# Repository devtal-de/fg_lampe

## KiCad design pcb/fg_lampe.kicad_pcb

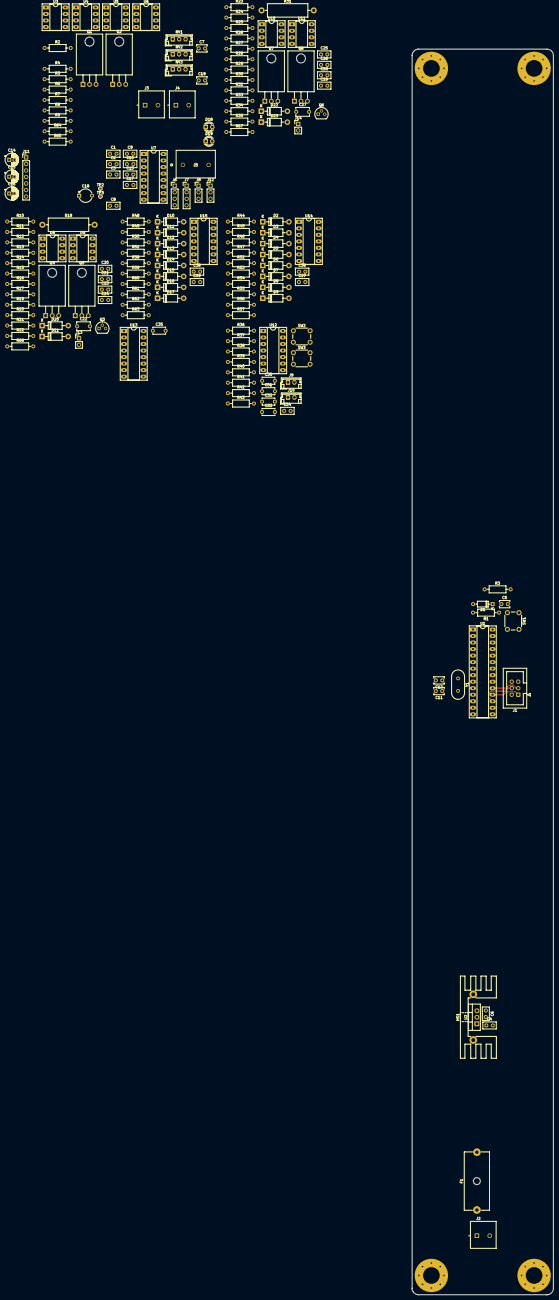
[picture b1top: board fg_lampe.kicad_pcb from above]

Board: 2 copper layers, 55.0 x 485.0 mm, 181 parts (0 on the bottom side), 110 nets.

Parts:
C1, C2, C3, C6, C8, C9, C10, C13, C17, C20, C21, C23, C24, C25, C26, C28, C29, C34, C36, C37, C38, C39: 0.1uF; C_Disc_D5.0mm_W2.5mm_P2.50mm
C4: 0.33uF; C_Disc_D5.0mm_W2.5mm_P2.50mm
C5: 10nF; C_Disc_D3.8mm_W2.6mm_P2.50mm
C7, C19: 1uF; C_Disc_D3.8mm_W2.6mm_P2.50mm
C11, C12: 22pF; C_Disc_D3.8mm_W2.6mm_P2.50mm
C14, C15, C16: 10uF; CP_Radial_D5.0mm_P2.00mm
C18: 10uF; CP_Radial_Tantal_D5.0mm_P5.00mm
C22, C27: 2.2nF; C_Disc_D5.1mm_W3.2mm_P5.00mm
C30, C31, C32, C33, C35: 1uF; C_Disc_D4.7mm_W2.5mm_P5.00mm
D1: 1N4148; D_DO-35_SOD27_P7.62mm_Horizontal
D2, D3, D4, D5, D6, D7, D8, D9, D10, D11, D12, D13, D14, D15, D16, D17, D20, D21, D22, D23: 1N5819; D_DO-41_SOD81_P10.16mm_Horizontal
D18, D19: LED; LED_D3.0mm
F1: Fuse; Fuseholder_Cylinder-5x20mm_Schurter_0031_8201_Horizontal_Op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
H1, H2, H3, H4: M6 Mounting Hole; MountingHole_6.5mm_Pad_Via
HS1: Heatsink_Pad; Heatsink_Stonecold_HS-132_32x14mm_2xFixation1.5mm
J1: ISP Port; IDC-Header_2x03_P2.54mm_Vertical
J2, J3, J4: 1792863; TE_1792863
J5: 1792876; CONN_1792876_PXC
J6: PWR Control; PinHeader_1x04_P2.54mm_Vertical
J7: RX/TX; PinHeader_1x04_P2.54mm_Vertical
J8: I^{2}C Debug; PinHeader_1x03_P2.54mm_Vertical
J9: External FG-Flex; JST_EH_B2B-EH-A_1x02_P2.50mm_Vertical
J10: External FG-One; JST_EH_B2B-EH-A_1x02_P2.50mm_Vertical
J11: SPI Debug Pins; PinHeader_1x07_P2.54mm_Vertical
J12: DAC Tespins; PinHeader_1x03_P2.54mm_Vertical
J13: Shunt Pin FG One; PinHeader_1x02_P2.54mm_Vertical
J14: Shunt Pin FG Flex; PinHeader_1x02_P2.54mm_Vertical
Q1, Q2: IRLZ540N; TO-220-3_Horizontal_TabDown
Q3, Q6: BC547; TO-92
Q4, Q5, Q7, Q8: IRF9540N; TO-220-3_Horizontal_TabDown
R1: 330R; R_Axial_DIN0207_L6.3mm_D2.5mm_P10.16mm_Horizontal
R2, R3, R4: 4.7k; R_Axial_DIN0207_L6.3mm_D2.5mm_P10.16mm_Horizontal
R5, R6, R9, R10, R11, R12, R13, R16, R19, R20, R23, R24, R25, R26, R29, R32, R33, R44, R45, R46, R47, R48, R49, R50, R51, R53, R54, R60, R61, R66, R67: 1k; R_Axial_DIN0207_L6.3mm_D2.5mm_P10.16mm_Horizontal
R7, R8, R17, R30: 100R; R_Axial_DIN0207_L6.3mm_D2.5mm_P10.16mm_Horizontal
R14, R15, R21, R22, R27, R28, R34, R35, R36, R37, R38, R39: 10k; R_Axial_DIN0207_L6.3mm_D2.5mm_P10.16mm_Horizontal
R18, R31: 0.1R; R_Axial_DIN0516_L15.5mm_D5.0mm_P20.32mm_Horizontal
R40, R41, R42, R43: 22k; R_Axial_DIN0207_L6.3mm_D2.5mm_P10.16mm_Horizontal
R52, R55, R62, R63: 33k; R_Axial_DIN0207_L6.3mm_D2.5mm_P10.16mm_Horizontal
R56, R59: 1.8k; R_Axial_DIN0207_L6.3mm_D2.5mm_P10.16mm_Horizontal
R57, R58: 7.5k; R_Axial_DIN0207_L6.3mm_D2.5mm_P10.16mm_Horizontal
R64, R65: 220R; R_Axial_DIN0207_L6.3mm_D2.5mm_P10.16mm_Horizontal
RV1: PWM_Cold_Poti; JST_EH_B3B-EH-A_1x03_P2.50mm_Vertical
RV2: PWM_Warm_Poti; JST_EH_B3B-EH-A_1x03_P2.50mm_Vertical
RV3: Angular_Position_Poti; JST_EH_B3B-EH-A_1x03_P2.50mm_Vertical
SW1: Reset Button; SW_PUSH_6mm_H5mm
SW2: FG-Flex Button; SW_PUSH_6mm_H5mm
SW3: FG-One Button; SW_PUSH_6mm_H5mm
TP2: V_{A} Testpoint; TestPoint_Pad_D1.0mm
TP3: V_{B} Testpoint; TestPoint_Pad_D1.0mm
U1: ATmega328P-P; DIP-28_W7.62mm_Socket_LongPads
U2: L7805; TO-220-3_Vertical
U3, U4: MAX1044; DIP-8_W7.62mm_Socket_LongPads
U5: MIC4427; DIP-8_W7.62mm_Socket_LongPads
U6: MCP4812; DIP-8_W7.62mm_Socket_LongPads
U7, U13: MCP3008; DIP-16_W7.62mm_Socket_LongPads
U8, U10: LM358; DIP-8_W7.62mm_Socket_LongPads
U9, U11: TL071; DIP-8_W7.62mm_Socket_LongPads
U12: 74HC14; DIP-14_W7.62mm_Socket_LongPads
U14, U15: LM324; DIP-14_W7.62mm_Socket_LongPads
Y1: 16MHz; Crystal_HC49-4H_Vertical

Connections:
+5V: C1.1, C3.1, C6.1, C7.1, C8.1, C9.1, C10.1, C13.1, C17.1, C18.1, C19.1, C34.1, C35.1, D1.1 (K), D2.1 (K), D4.1 (K), D6.1 (K), D8.1 (K), D10.1 (K), D12.1 (K), D14.1 (K), D16.1 (K), D20.1 (K), D22.1 (K), J1.2, J6.3, J7.4, R2.1, R3.1, R4.1, R36.1, R37.1, R38.1, R39.1, RV1.1, RV2.1, RV3.1, U1.7 (VCC), U1.20 (AVCC), U2.3 (OUT), U3.8 (V+), U4.8 (V+), U5.6 (V+), U6.1 (Vdd), U7.15 (Vref), U7.16 (Vdd), U12.14 (VCC), U13.15 (Vref), U13.16 (Vdd)
+24V: C4.1, C20.1, C23.1, C25.1, C28.1, C36.1, C38.1, F1.2, J5.1, J6.4, Q4.3 (S), Q7.3 (S), R11.1, R14.1, R25.1, R27.1, U2.1 (IN), U8.8 (V+), U9.7 (V+), U10.8 (V+), U11.7 (V+), U14.4 (V+), U15.4 (V+)
-5V: C16.2, C21.1, C24.1, C26.1, C29.1, C37.1, C39.1, J6.1, U3.5 (VOUT), U4.5 (VOUT), U8.4 (V-), U9.4 (V-), U10.4 (V-), U11.4 (V-), U14.11 (V-), U15.11 (V-)
/AREF: C2.1, U1.21 (AREF)
/Angular_Position: R9.2, U7.7 (CH6)
/Buttons and Inputs/Activate FG-Flex: U1.5 (PD3), U12.2
/Buttons and Inputs/Activate FG-One: U1.4 (PD2), U12.4
/Buttons and Inputs/Ext. Activate FG-Flex: U1.11 (PD5), U12.6
/Buttons and Inputs/Ext. Activate FG-One: U1.6 (PD4), U12.8
/FG-Flex Current Source/Inv Input U7B: C27.1, R23.2, R29.1, U10.6 (-)
/FG-Flex Current Source/Non-Inv Input U7B: R25.2, R26.1, U10.5 (+)
/FG-Flex Current Source/Q4_Base: Q6.2 (B), R24.2
/FG-Flex Current Source/Q4_Collector: Q6.1 (C), R28.2
/FG-Flex Current Source/Q5_Gate: Q7.1 (G), R27.2, R28.1
/FG-Flex Current Source/U7A Voltage follower: R23.1, U10.1, U10.2 (-)
/FG-One Current Source/Inv Input U6B: C22.1, R10.2, R16.1, U8.6 (-)
/FG-One Current Source/Non-Inv Input U6B: R11.2, R12.1, U8.5 (+)
/FG-One Current Source/Q1_Base: Q3.2 (B), R13.2
/FG-One Current Source/Q1_Collector: Q3.1 (C), R15.2
/FG-One Current Source/Q2_Gate: Q4.1 (G), R14.2, R15.1
/FG-One Current Source/U6A Voltage follower: R10.1, U8.1, U8.2 (-)
/FG-One Current Source/U6_output: C22.2, R17.1, U8.7
/I_FG_Flex: J4.1, Q8.2 (D), R57.2, U14.3 (+), U14.5 (+), U14.10 (+)
/I_FG_One: J3.1, Q5.2 (D), R58.2, U15.3 (+), U15.5 (+), U15.10 (+)
/LED1: R64.1, U1.23 (PC0)
/LED2: R65.1, U1.24 (PC1)
/MISO: J1.1, J11.3, U1.18 (PB4), U7.12 (Dout), U13.12 (Dout)
/MOSI: J1.4, J11.4, U1.17 (PB3), U6.4 (SDI), U7.11 (Din), U13.11 (Din)
/PWR_in: F1.1, J2.1
/RX: J7.3, U1.2 (PD0)
/R_Value_Cold: R5.2, U7.6 (CH5)
/R_Value_Warm: R6.2, U7.5 (CH4)
/SCK: J1.3, J11.2, U1.19 (PB5), U6.3 (SCK), U7.13 (CLK), U13.13 (CLK)
/SCL: J8.3, R4.2, U1.28 (PC5)
/SDA: J8.2, R2.2, U1.27 (PC4)
/SMA Measurement/FG Flex Voltage Sensing/FG_FLEX_G8: D4.2 (A), D5.1 (K), R45.2, U13.2 (CH1)
/SMA Measurement/FG Flex Voltage Sensing/FG_FLEX_G34: D2.2 (A), D3.1 (K), R44.2, U13.1 (CH0)
/SMA Measurement/FG Flex Voltage Sensing/FG_FLEX_SP: D6.2 (A), D7.1 (K), R46.2, U13.3 (CH2)
/SMA Measurement/FG Flex Voltage Sensing/FG_FLEX_WS: D8.2 (A), D9.1 (K), R47.2, U13.4 (CH3)
/SMA Measurement/FG One Voltage Sensing/FG_One_G8: D12.2 (A), D13.1 (K), R49.2, U13.6 (CH5)
/SMA Measurement/FG One Voltage Sensing/FG_One_G34: D10.2 (A), D11.1 (K), R48.2, U13.5 (CH4)
/SMA Measurement/FG One Voltage Sensing/FG_One_SP: D14.2 (A), D15.1 (K), R50.2, U13.7 (CH6)
/SMA Measurement/FG One Voltage Sensing/FG_One_WS: D16.2 (A), D17.1 (K), R51.2, U13.8 (CH7)
/TX: J7.2, U1.3 (PD1)
/U3_CAP+: C14.1, U3.2 (CAP+)
/U3_CAP-: C14.2, U3.4 (CAP-)
/U4_CAP+: C15.1, U4.2 (CAP+)
/U4_CAP-: C15.2, U4.4 (CAP-)
/V_{A}: J12.3, TP2.1, U6.8 (VA), U7.1 (CH0), U8.3 (+)
/V_{B}: J12.1, TP3.1, U6.6 (VB), U7.2 (CH1), U10.3 (+)
/XTAL1: C12.1, U1.9 (XTAL1/PB6), Y1.1
/XTAL2: C11.1, U1.10 (XTAL2/PB7), Y1.2
/activate fg_flex: R24.1, U1.25 (PC2)
/activate fg_one: R13.1, U1.26 (PC3)
/cold_driver: U1.13 (PD7), U5.4 (IN_B)
/cold_led_to_gnd: J5.3, Q2.2 (D)
/cold_pwm: R8.1, U5.5 (OUT_B)
/shunt_fg-flex: D22.2 (A), D23.1 (K), R67.2, U7.4 (CH3)
/shunt_fg-one: D20.2 (A), D21.1 (K), R66.2, U7.3 (CH2)
/warm_driver: U1.12 (PD6), U5.2 (IN_A)
/warm_led_to_gnd: J5.2, Q1.2 (D)
/warm_pwm: R7.1, U5.7 (OUT_A)
/~RESET: C5.1, D1.2 (A), J1.5, R1.2, R3.2, U1.1 (~RESET/PC6)
/~SS1: J11.7, U1.16 (PB2), U6.2 (~CS)
/~SS2: J11.6, U1.15 (PB1), U7.10 (~CS/SHDN)
/~SS3: J11.5, U1.14 (PB0), U13.10 (~CS/SHDN)
GND: C1.2, C2.2, C3.2, C4.2, C5.2, C6.2, C7.2, C8.2, C9.2, C10.2, C11.2, C12.2, C13.2, C16.1, C17.2, C18.2, C19.2, C20.2, C21.2, C23.2, C24.2, C25.2, C26.2, C28.2, C29.2, C30.2, C31.2, C32.2, C33.2, C34.2, C35.2, C36.2, C37.2, C38.2, C39.2, D3.2 (A), D5.2 (A), D7.2 (A), D9.2 (A), D11.2 (A), D13.2 (A), D15.2 (A), D17.2 (A), D18.1 (K), D19.1 (K), D21.2 (A), D23.2 (A), H1.1, H2.1, H3.1, H4.1, J1.6, J2.2, J3.2, J4.2, J6.2, J7.1, J8.1, J9.2, J10.2, J11.1, J12.2, Q1.3 (S), Q2.3 (S), Q3.3 (E), Q6.3 (E), R12.2, R21.2, R26.2, R34.2, R53.1, R54.1, R56.1, R59.1, R60.1, R61.1, RV1.3, RV2.3, RV3.3, SW1.1, SW2.1, SW3.1, U1.8 (GND), U1.22 (GND), U2.2 (GND), U3.3 (GND), U4.3 (GND), U5.3 (GND), U6.5 (~LDAC), U6.7 (Vss), U7.9 (DGND), U7.14 (AGND), U12.7 (GND), U12.11, U12.13, U13.9 (DGND), U13.14 (AGND)
unnamed: C27.2, R30.1, U10.7
unnamed: C30.1, R40.2, U12.1
unnamed: C31.1, R41.2, U12.3
unnamed: C32.1, R42.2, U12.5
unnamed: C33.1, R43.2, U12.9
unnamed: D18.2 (A), R64.2
unnamed: D19.2 (A), R65.2
unnamed: J9.1, R38.2, R42.1
unnamed: J10.1, R39.2, R43.1
unnamed: J13.1, Q5.3 (S), R16.2, R18.2, R20.1
unnamed: J13.2, Q4.2 (D), R18.1, R19.1
unnamed: J14.1, Q8.3 (S), R29.2, R31.2, R33.1
unnamed: J14.2, Q7.2 (D), R31.1, R32.1
unnamed: Q1.1 (G), R7.2
unnamed: Q2.1 (G), R8.2
unnamed: Q5.1 (G), R17.2
unnamed: Q8.1 (G), R30.2
unnamed: R1.1, SW1.2
unnamed: R5.1, RV1.2
unnamed: R6.1, RV2.2
unnamed: R9.1, RV3.2
unnamed: R22.2, R66.1, U9.6
unnamed: R35.2, R67.1, U11.6
unnamed: R36.2, R40.1, SW2.2
unnamed: R37.2, R41.1, SW3.2
unnamed: R44.1, R52.2, U14.1
unnamed: R45.1, R55.2, U14.7
unnamed: R48.1, R62.2, U15.1
unnamed: R49.1, R63.2, U15.7
unnamed: R19.2, R21.1, U9.3 (+)
unnamed: R20.2, R22.1, U9.2 (-)
unnamed: R32.2, R34.1, U11.3 (+)
unnamed: R33.2, R35.1, U11.2 (-)
unnamed: R52.1, R53.2, U14.2 (-)
unnamed: R54.2, R55.1, U14.6 (-)
unnamed: R46.1, U14.8, U14.9 (-)
unnamed: R56.2, R57.1, U14.12 (+)
unnamed: R47.1, U14.13 (-), U14.14
unnamed: R60.2, R62.1, U15.2 (-)
unnamed: R61.2, R63.1, U15.6 (-)
unnamed: R50.1, U15.8, U15.9 (-)
unnamed: R58.1, R59.2, U15.12 (+)
unnamed: R51.1, U15.13 (-), U15.14

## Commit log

2023-11-03 Gitignore for KiCad added
2023-11-03 first schematics added
2023-11-03 gitignore changes to ignore more autosave files from KiCad
2023-11-03 negative voltage charge pump added and some minor fixes
2023-11-03 start with implementing current sources to controll the sma wires
2023-11-05 current sources added
2023-11-05 mcp3008 finished integrating
2023-11-06 current shunt measurement added
2023-11-07 shunt measurement changed to different opamp
2023-11-08 connector added
2023-11-10 reset button integrated
2023-11-15 Init platformio
2023-11-16 buttons included
2023-11-16 gitignore modified
2023-11-16 first lib includes
2023-11-16 more stuff corrected
2023-11-22 potentiometer to set pwm for warm and cold light added
2023-11-24 gate driver added
2023-11-25 mosfet for LEDs added
2023-12-07 vcc changed with +24V
2023-12-08 minor changes
2023-12-08 sma measurement added, new connector for leds, some minor fixes
2023-12-09 final version schematic?
2023-12-10 finals in schematic
2023-12-11 start pcb
